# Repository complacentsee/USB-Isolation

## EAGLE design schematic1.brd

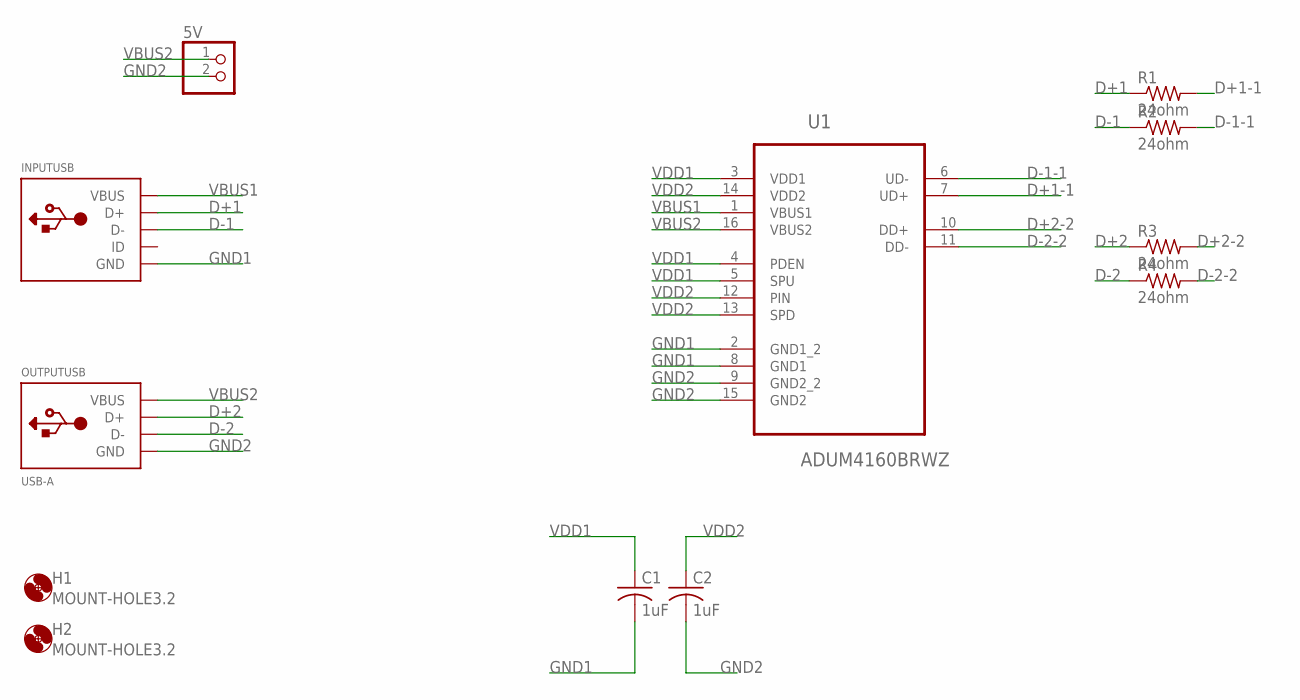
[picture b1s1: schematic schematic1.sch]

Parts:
5V: PINHD-1X2; 1X02
C1, C2: 1uF; C0805
H1, H2: MOUNT-HOLE3.2; 3,2
INPUTUSB: USBMINIB; USB-MINIB
OUTPUTUSB: USB-A; MOLEX_480371000
R1, R2, R3, R4: 24ohm; R0805
U1: ADUM4160BRWZ; SOIC127P1032X265-16N

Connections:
D+1: INPUTUSB.D+, R1.1
D+1-1: R1.2, U1.7 (UD+)
D+2: OUTPUTUSB.3 (D+), R3.1
D+2-2: R3.2, U1.10 (DD+)
D-1: INPUTUSB.D-, R2.1
D-1-1: R2.2, U1.6 (UD-)
D-2: OUTPUTUSB.2 (D-), R4.1
D-2-2: R4.2, U1.11 (DD-)
GND1: C1.2, INPUTUSB.GND, U1.2 (GND1_2), U1.8 (GND1)
GND2: 5V.2, C2.2, OUTPUTUSB.4 (GND), U1.9 (GND2_2), U1.15 (GND2)
VBUS1: INPUTUSB.VBUS, U1.1 (VBUS1)
VBUS2: 5V.1, OUTPUTUSB.1 (VBUS), U1.16 (VBUS2)
VDD1: C1.1, U1.3 (VDD1), U1.4 (PDEN), U1.5 (SPU)
VDD2: C2.1, U1.12 (PIN), U1.13 (SPD), U1.14 (VDD2)

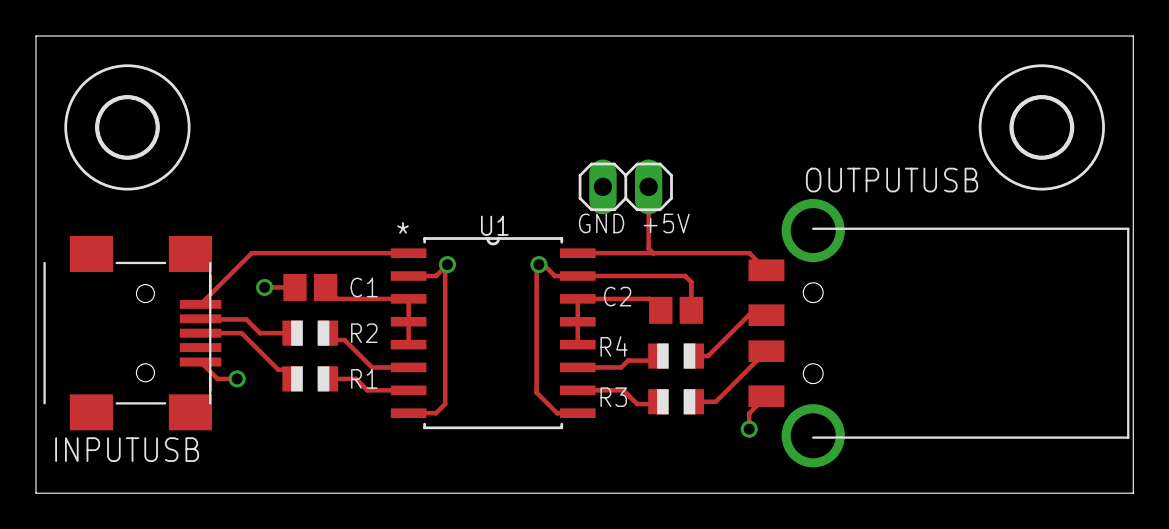
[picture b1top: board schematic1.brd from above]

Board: 2 copper layers, 61.0 x 25.4 mm, 12 parts (0 on the bottom side), 14 nets.

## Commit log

2014-11-23 added schematics and board files
